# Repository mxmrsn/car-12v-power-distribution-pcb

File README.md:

# Car 12V Power Distribution PCB
12V distribution block for supporting interior automotive (12V+) accessories. Note: Some accesories mentioned such as dashcam and charger have downstream 5V regulators. Molex PicoSpox contacts (0874370231) are rated for 3A each with 24AWG wire.

## Notes
- Footprints are Molex PicoSpoX-style SMD 1.5mm pitch footprints. 
- Inputs:
  - `12V+` (+12V battery)
  - `12V_ACC` (+12V accessory)
  - `GND` (ground)
- Output (3-pin): `+12V`, `+12V_ACC`, `GND`
- Output (4-pin): `+12V`, `+12V_ACC`, `+12V_HEADLIGHT`, `GND`
- PCB uses 40 mil traces for all nets. 
- Board outline is 1.5" x 2".
- 3D printed caddy will require strain relief and a mobile loop of wire to move with the opening/closing of the drawer.

## Schematic

## PCB Layout

## 3D Model

## BOM
- 3-pin connector [Molex #0874370363](https://www.digikey.com/en/products/detail/molex/0874370363/2834835)
- 4-pin connector [Molex 0874370473](https://www.digikey.com/en/products/detail/molex/0874370473/2421923)

Mating connectors (cable-side):
- 3-pin housing [Molex #0874390300](https://www.digikey.com/en/products/detail/molex/0874390300/561766)
- 4-pin housing [Molex #0874390400](https://www.digikey.com/en/products/detail/molex/0874390400/561767)
- Molex PicoSpox Contact [Molex #0874210000](https://www.digikey.com/en/products/detail/molex/0874210000/561764)

## Reference
- [Molex PicoSpox Wire-to-Board Connectors](https://www.digikey.com/en/product-highlight/m/molex-connector/pico-spox-wire-to-board-connector-system)

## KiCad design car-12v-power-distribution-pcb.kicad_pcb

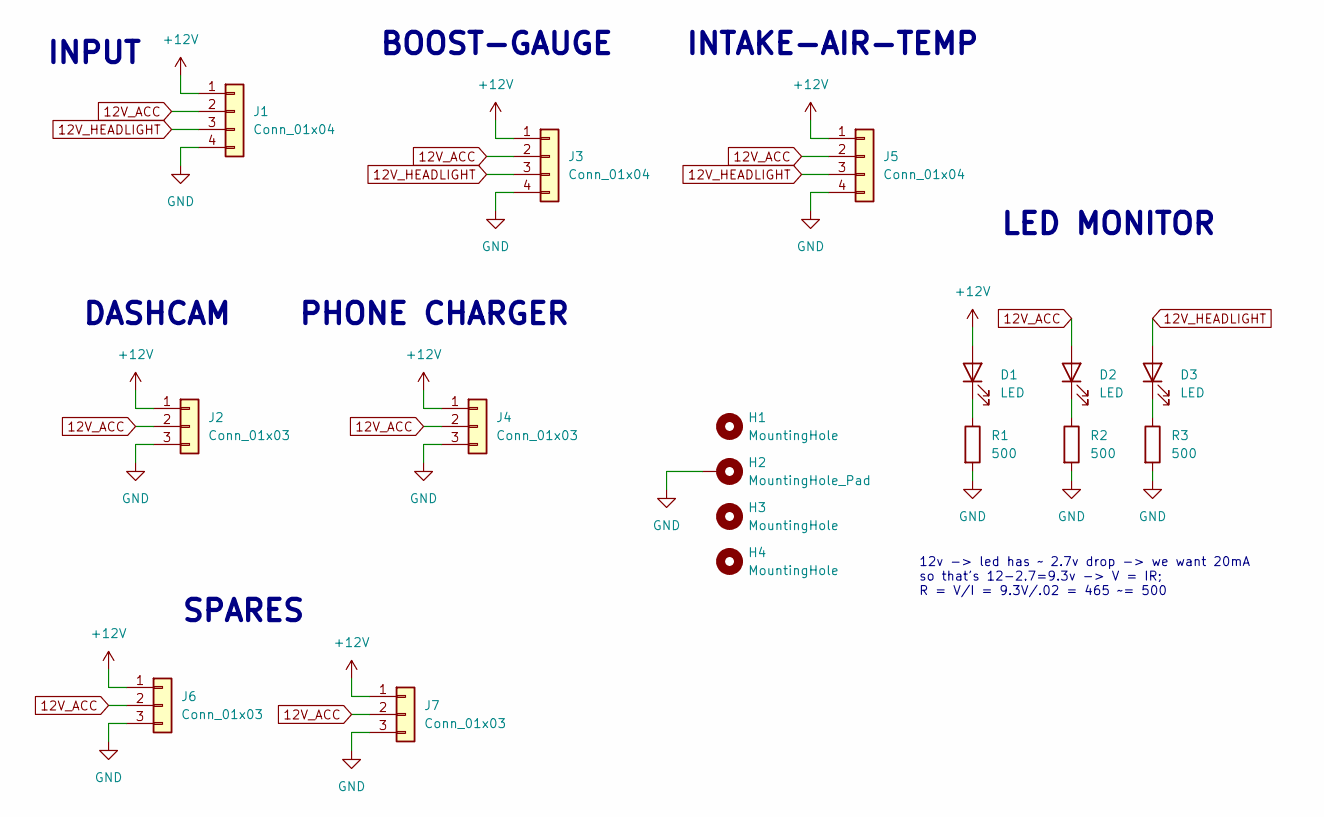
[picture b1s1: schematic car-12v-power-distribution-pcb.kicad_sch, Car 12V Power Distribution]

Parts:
D1, D2, D3: LED; LED_0603_1608Metric; LCSC C2286
H1, H3, H4: MountingHole; MountingHole_2.7mm_M2.5
H2: MountingHole_Pad; MountingHole_2.5mm_Pad_TopBottom
J1, J3, J5: Conn_01x04; CONN_874370231-SD_04_MOL; LCSC C588581
J2, J4, J6, J7: Conn_01x03; CONN_874370231-SD_03_MOL; LCSC C17393004
R1, R2, R3: 500; R_0603_1608Metric; LCSC C860931

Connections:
12V_ACC: D2.2 (A), J1.2, J2.2, J3.2, J4.2, J5.2, J6.2, J7.2
12V_HEADLIGHT: D3.2 (A), J1.3, J3.3, J5.3
+12V: D1.2 (A), J1.1, J2.1, J3.1, J4.1, J5.1, J6.1, J7.1
GND: H2.1, J1.4, J2.3, J3.4, J4.3, J5.4, J6.3, J7.3, R1.2, R2.2, R3.2
unnamed: D1.1 (K), R1.1
unnamed: D2.1 (K), R2.1
unnamed: D3.1 (K), R3.1

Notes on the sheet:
12v -> led has ~ 2.7v drop -> we want 20mA so that's 12-2.7=9.3v -> V = IR; R = V/I = 9.3V/.02 = 465 ~= 500
PHONE CHARGER
SPARES
INTAKE-AIR-TEMP
INPUT
DASHCAM
LED MONITOR
BOOST-GAUGE

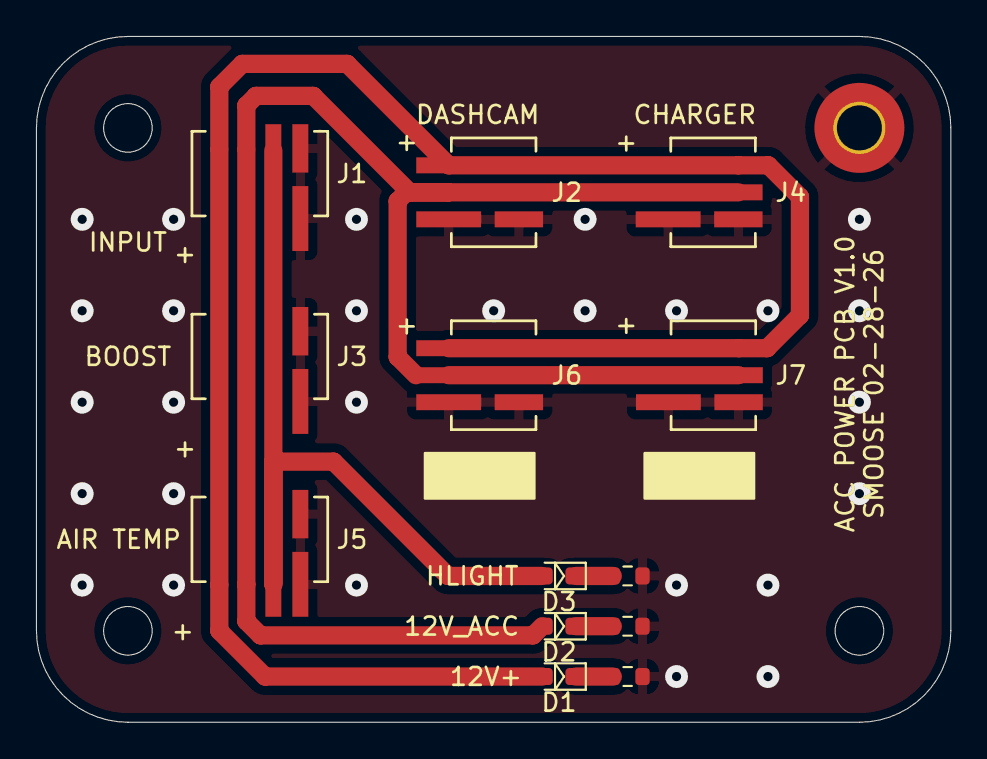
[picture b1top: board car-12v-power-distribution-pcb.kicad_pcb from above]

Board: 2 copper layers, 50.8 x 38.1 mm, 17 parts (0 on the bottom side), 7 nets.

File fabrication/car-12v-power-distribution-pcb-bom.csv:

Comment,Designator,Footprint,LCSC Part #
LED Light emitting diode,"D1,D2,D3",LED_0603_1608Metric,C2286
"Conn_01x04 Generic connector, single row, 01x04, script generated (kicad-library-utils/schlib/autogen/connector/)","J1,J3,J5",CONN_874370231-SD_04_MOL,C588581
"Conn_01x03 Generic connector, single row, 01x03, script generated (kicad-library-utils/schlib/autogen/connector/)","J2,J4,J6,J7",CONN_874370231-SD_03_MOL,C17393004
500 Resistor,"R1,R2,R3",R_0603_1608Metric,C860931

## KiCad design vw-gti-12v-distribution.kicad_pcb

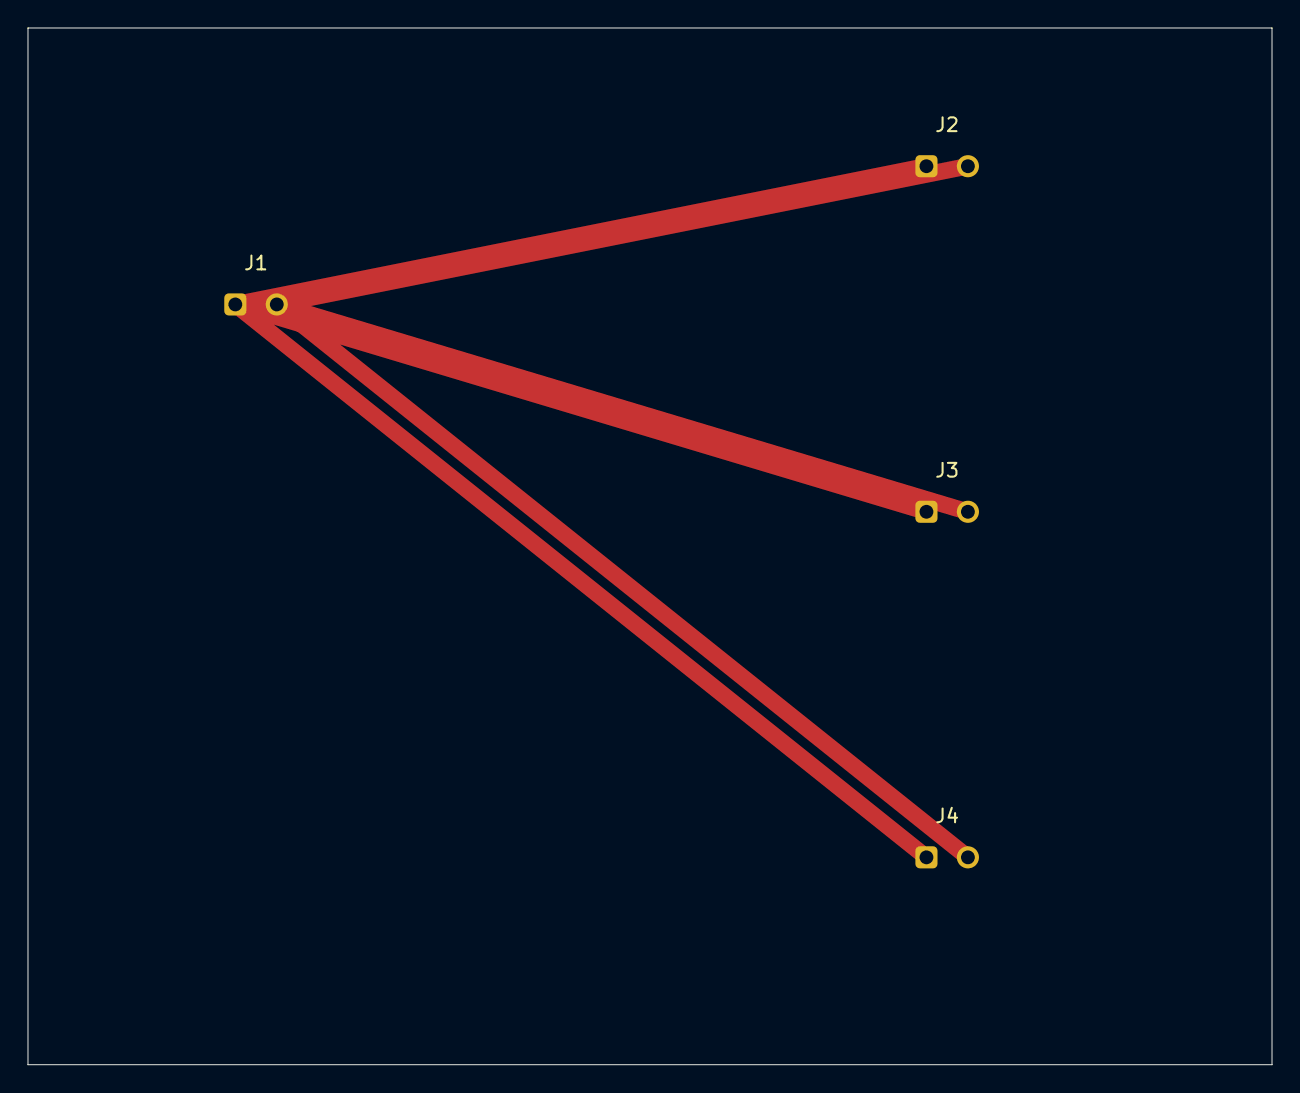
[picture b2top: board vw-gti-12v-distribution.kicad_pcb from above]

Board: 2 copper layers, 90.0 x 75.0 mm, 4 parts (0 on the bottom side), 2 nets.

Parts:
J1: IN_12V; PicoSpoX_1x02_P3.00mm_THT
J2: OUT_DASHCAM; PicoSpoX_1x02_P3.00mm_THT
J3: OUT_PHONE; PicoSpoX_1x02_P3.00mm_THT
J4: OUT_BOOST; PicoSpoX_1x02_P3.00mm_THT

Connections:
+12V: J1.1, J2.1, J3.1, J4.1
GND: J1.2, J2.2, J3.2, J4.2

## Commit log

2026-02-28 Initial 12V distribution PCB
2026-02-28 Switch to SMD PicoSpoX and add ACC + extra outputs
2026-02-28 Rename project to car-12v-power-distribution-pcb
2026-02-28 Downgrade schematic format for KiCad 6
2026-02-28 Remove hide flags for KiCad 6 compatibility
2026-02-28 Strip footprint properties for KiCad 6 PCB
2026-02-28 Reset to blank KiCad 6 schematic and PCB
2026-02-28 version 1.0
2026-02-28 Add schematic and layout screenshots to README
2026-02-28 Add 3D screenshot to README
2026-02-28 Add gerbers archive
2026-02-28 updated readme file dirs
2026-02-28 added .gitignore and footprints/
2026-02-28 updated grounding hole
2026-02-28 added bom and cpl files
